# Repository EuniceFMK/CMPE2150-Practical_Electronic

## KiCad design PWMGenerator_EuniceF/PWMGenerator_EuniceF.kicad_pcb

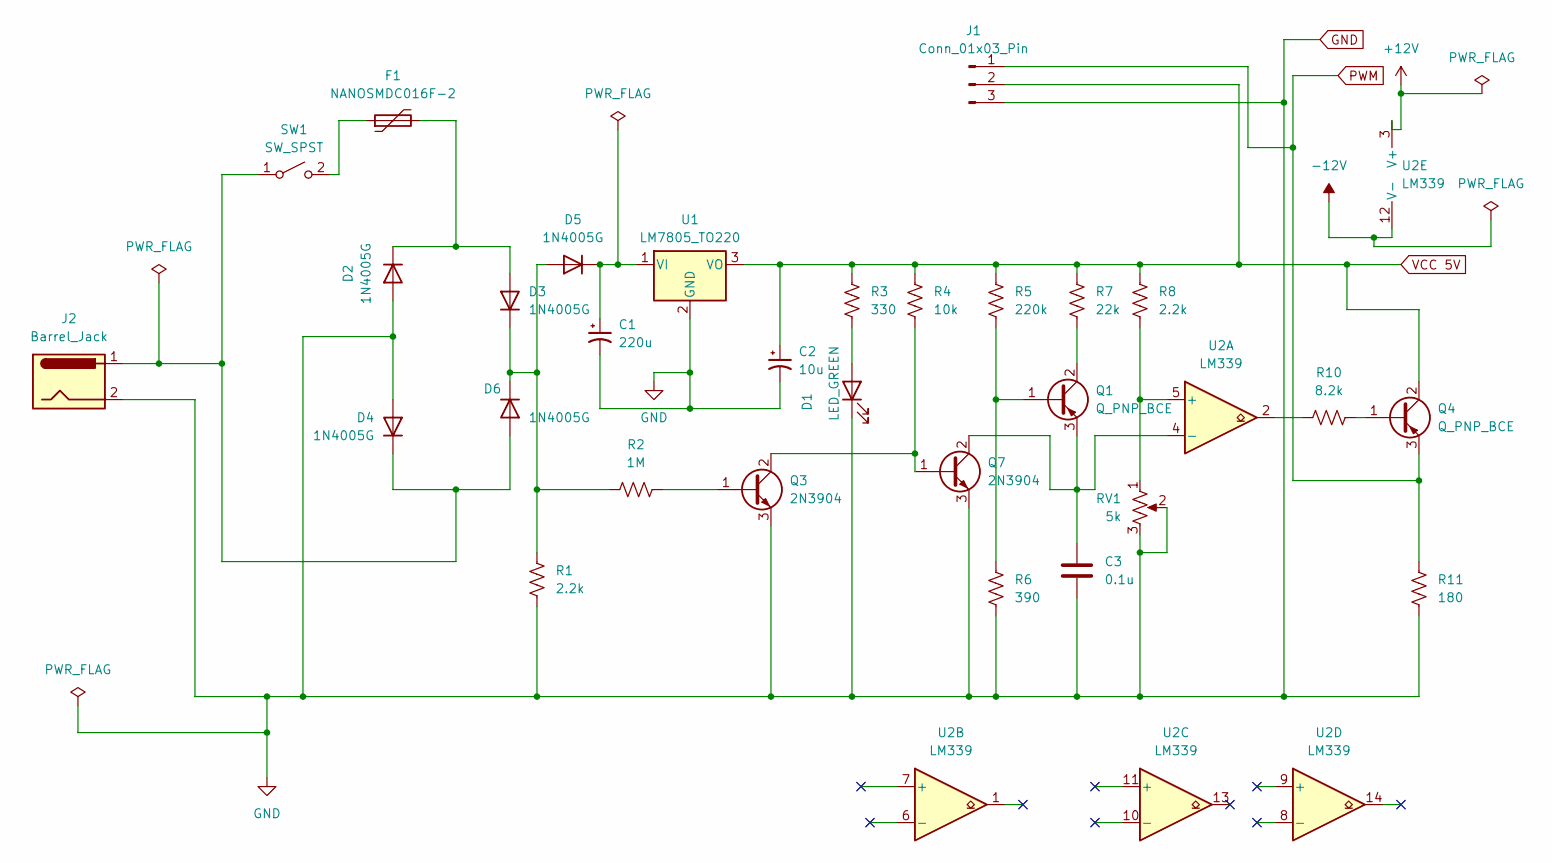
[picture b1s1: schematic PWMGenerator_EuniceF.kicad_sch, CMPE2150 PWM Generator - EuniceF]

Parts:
C1: 220u; C_Disc_D12.5mm_W5.0mm_P10.00mm
C2: 10u; C_Disc_D12.5mm_W5.0mm_P10.00mm
C3: 0.1u; C_0805_2012Metric
D1: LED_GREEN; LED_D5.0mm-4_RGB
D2, D4, D5, D6: 1N4005G; D_0805_2012Metric
D3: 1N4005G; D_DO-41_SOD81_P10.16mm_Horizontal
F1: NANOSMDC016F-2; RESC3115X65N
J1: Conn_01x03_Pin; PinHeader_1x03_P2.54mm_Horizontal
J2: Barrel_Jack; BarrelJack_CUI_PJ-063AH_Horizontal
Q1, Q4: Q_PNP_BCE; SOT-23
Q3, Q7: 2N3904; SOT-23
R1, R8: 2.2k; R_0805_2012Metric
R2: 1M; R_0805_2012Metric
R3: 330; R_0805_2012Metric
R4: 10k; R_0805_2012Metric
R5: 220k; R_0805_2012Metric
R6: 390; R_0805_2012Metric
R7: 22k; R_0805_2012Metric
R10: 8.2k; R_0805_2012Metric
R11: 180; R_0805_2012Metric
RV1: 5k; Potentiometer_ACP_CA14-H2,5_Horizontal
SW1: SW_SPST; SW_DIP_SPSTx01_Slide_6.7x4.1mm_W6.73mm_P2.54mm_LowProfile_J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
U1: LM7805_TO220; TO-220-3_Horizontal_TabDown
U2: LM339; SOIC-14_3.9x8.7mm_P1.27mm

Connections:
+12V: U2.3 (V+)
-12V: U2.12 (V-)
GND: C1.2, C2.2, C3.2, D1.1 (K), D2.2 (A), D4.2 (A), J1.3, J2.2, Q3.3 (E), Q7.3 (E), R1.2, R6.2, R11.2, RV1.2, RV1.3, U1.2 (GND)
unnamed: D1.2 (A), R3.2
unnamed: D2.1 (K), D3.2 (A), F1.2
unnamed: D3.1 (K), D5.2 (A), D6.1 (K), R1.1, R2.1
unnamed: D4.1 (K), D6.2 (A), J2.1, SW1.1 (A)
unnamed: C1.1, D5.1 (K), U1.1 (VI)
unnamed: Q1.1 (B), R5.2, R6.1
unnamed: Q1.2 (C), R7.2
unnamed: C3.1, Q1.3 (E), Q7.2 (C), U2.4 (-)
unnamed: Q3.1 (B), R2.2
unnamed: Q3.2 (C), Q7.1 (B), R4.2
unnamed: Q4.1 (B), R10.2
unnamed: R10.1, U2.2
unnamed: F1.1, SW1.2 (B)
unnamed: R8.2, RV1.1, U2.5 (+)
PWM: J1.1, Q4.3 (E), R11.1
VCC 5V: C2.1, J1.2, Q4.2 (C), R3.1, R4.1, R5.1, R7.1, R8.1, U1.3 (VO)

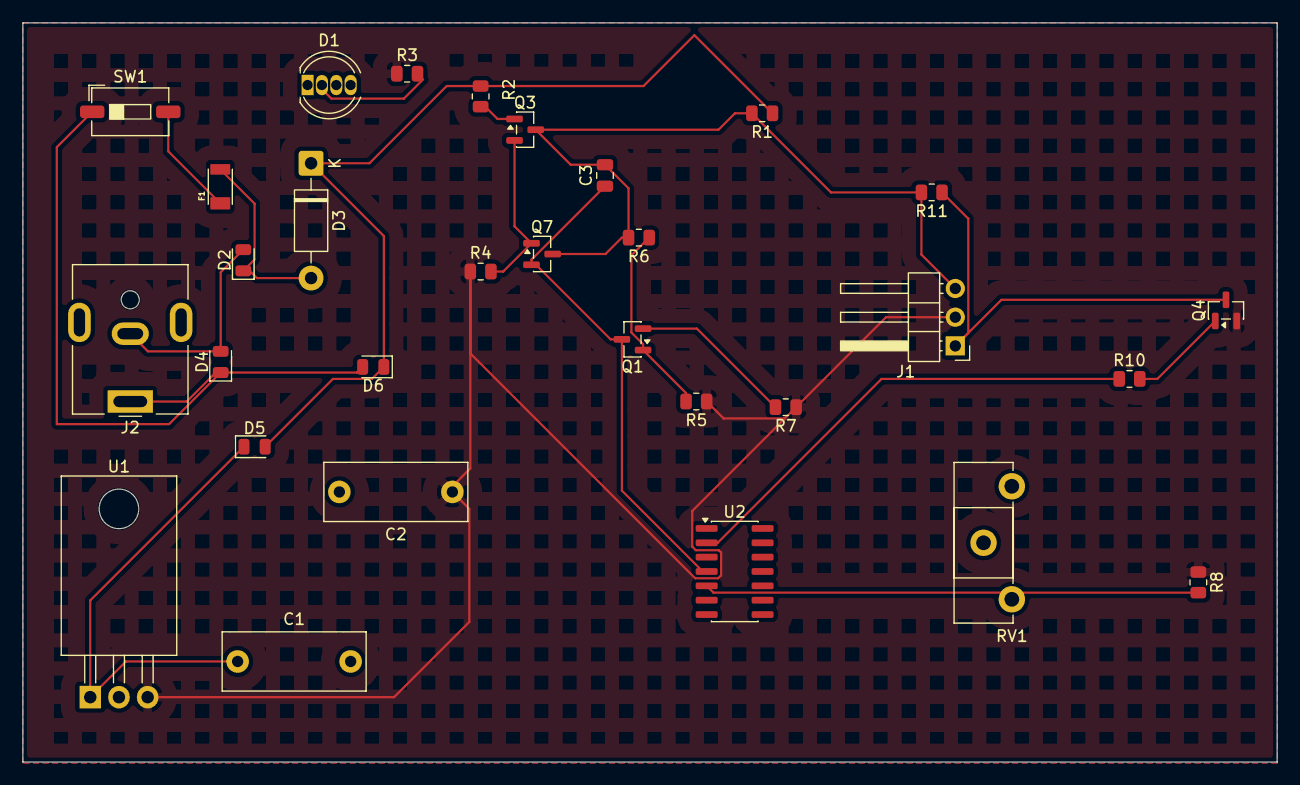
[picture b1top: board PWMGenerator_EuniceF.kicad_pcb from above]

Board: 2 copper layers, 111.0 x 65.4 mm, 30 parts (0 on the bottom side), 17 nets.

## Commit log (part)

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2026-01-14 Add IO Configurations notes PDF
    Added CMPE2150.Notes.01.IOConfigurations.pdf to the Notes directory for reference.
2026-01-19 Add Multisim SA2.ms14 project file
    Added a new Multisim project file 'Multisim SA2.ms14' to the repository.
2026-01-19 LAB1 Multisim
2026-01-19 Remove IO Configurations PDF from notes
    Deleted CMPE2150.Notes.01.IOConfigurations.pdf from the Notes directory. This may be due to outdated content or to reduce repository size.
2026-01-21 Update LAB_1 Multisim
2026-01-28 Syllabus commit
2026-02-02 LAB1 MULTISIM PART B
2026-02-02 LAB 1
2026-04-09 PCBA Project
2026-04-10 PWMGenerator
2026-04-10 PCB Part B
2026-04-14 PCB Part C COMMIT
2026-04-14 PCB PARTC WORKING
2026-04-15 Partc Final working
2026-05-21 Photo commit
